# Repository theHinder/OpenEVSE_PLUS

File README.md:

# OpenEVSE_PLUS
README.md for OpenEVSE Hardware
Files SCH and BRD in Eagle format
License CC BY-SA 3.0
OpenEVSE Hardware

Current Version OpenEVSE_PLUS_v5.5.

OpenEVSE_PLUS_V5.5 - Moved GFCI Test pin to enable move of DC Relay outputs to PWM capable pins supporting full power closing reduced power holding in OpenEVSE 7.1.2+ firmware. Added GPIO pin pulled HIGH to auto detect board version in software to automatically set new/old pin values without requiring different firmware. Replaced 0.1" generic non-polarized connectors with JST PH for Serial (WiFi) and i2c (Display). Combined power and data connections for WiFi to reduce eliminate a screw terminal connector and simplify wiring harness. Replaced DC/DC converter with a TC1044S invert chip to generate -12v from +12v. 

OpenEVSE_PLUS_v5 - Optimized for reduced build time and high volume manufacturing of changing stations, removed most screw terminals and replaced with common connectors. Change from 2 single chanel opto-isolators for AC detection to 1 dual channel. Added ground connections to screw holes.

OpenEVSE_PLUS_v4 - Has 2 AC Detect chips like v1 + v2 plus the AC relay driver of v3. Added rectifier diodes to AC detect to improve detection in some conditions. Changed GFCI to individual pinout 4 pins.

OpenEVSE_PLUS_v3 - Removed 1 AC Detect chip and added AC relay driver. Added Current measurement circuit

OpenEVSE_PLUS_v2.5 - Added Current measurement circuit.

OpenEVSE_PLUS_v2 - modified GFCI pinout

OpenEVSE_PLUS_v1 - Inital version - Combined OpenEVSE v7 board and Advanced power supply into single board

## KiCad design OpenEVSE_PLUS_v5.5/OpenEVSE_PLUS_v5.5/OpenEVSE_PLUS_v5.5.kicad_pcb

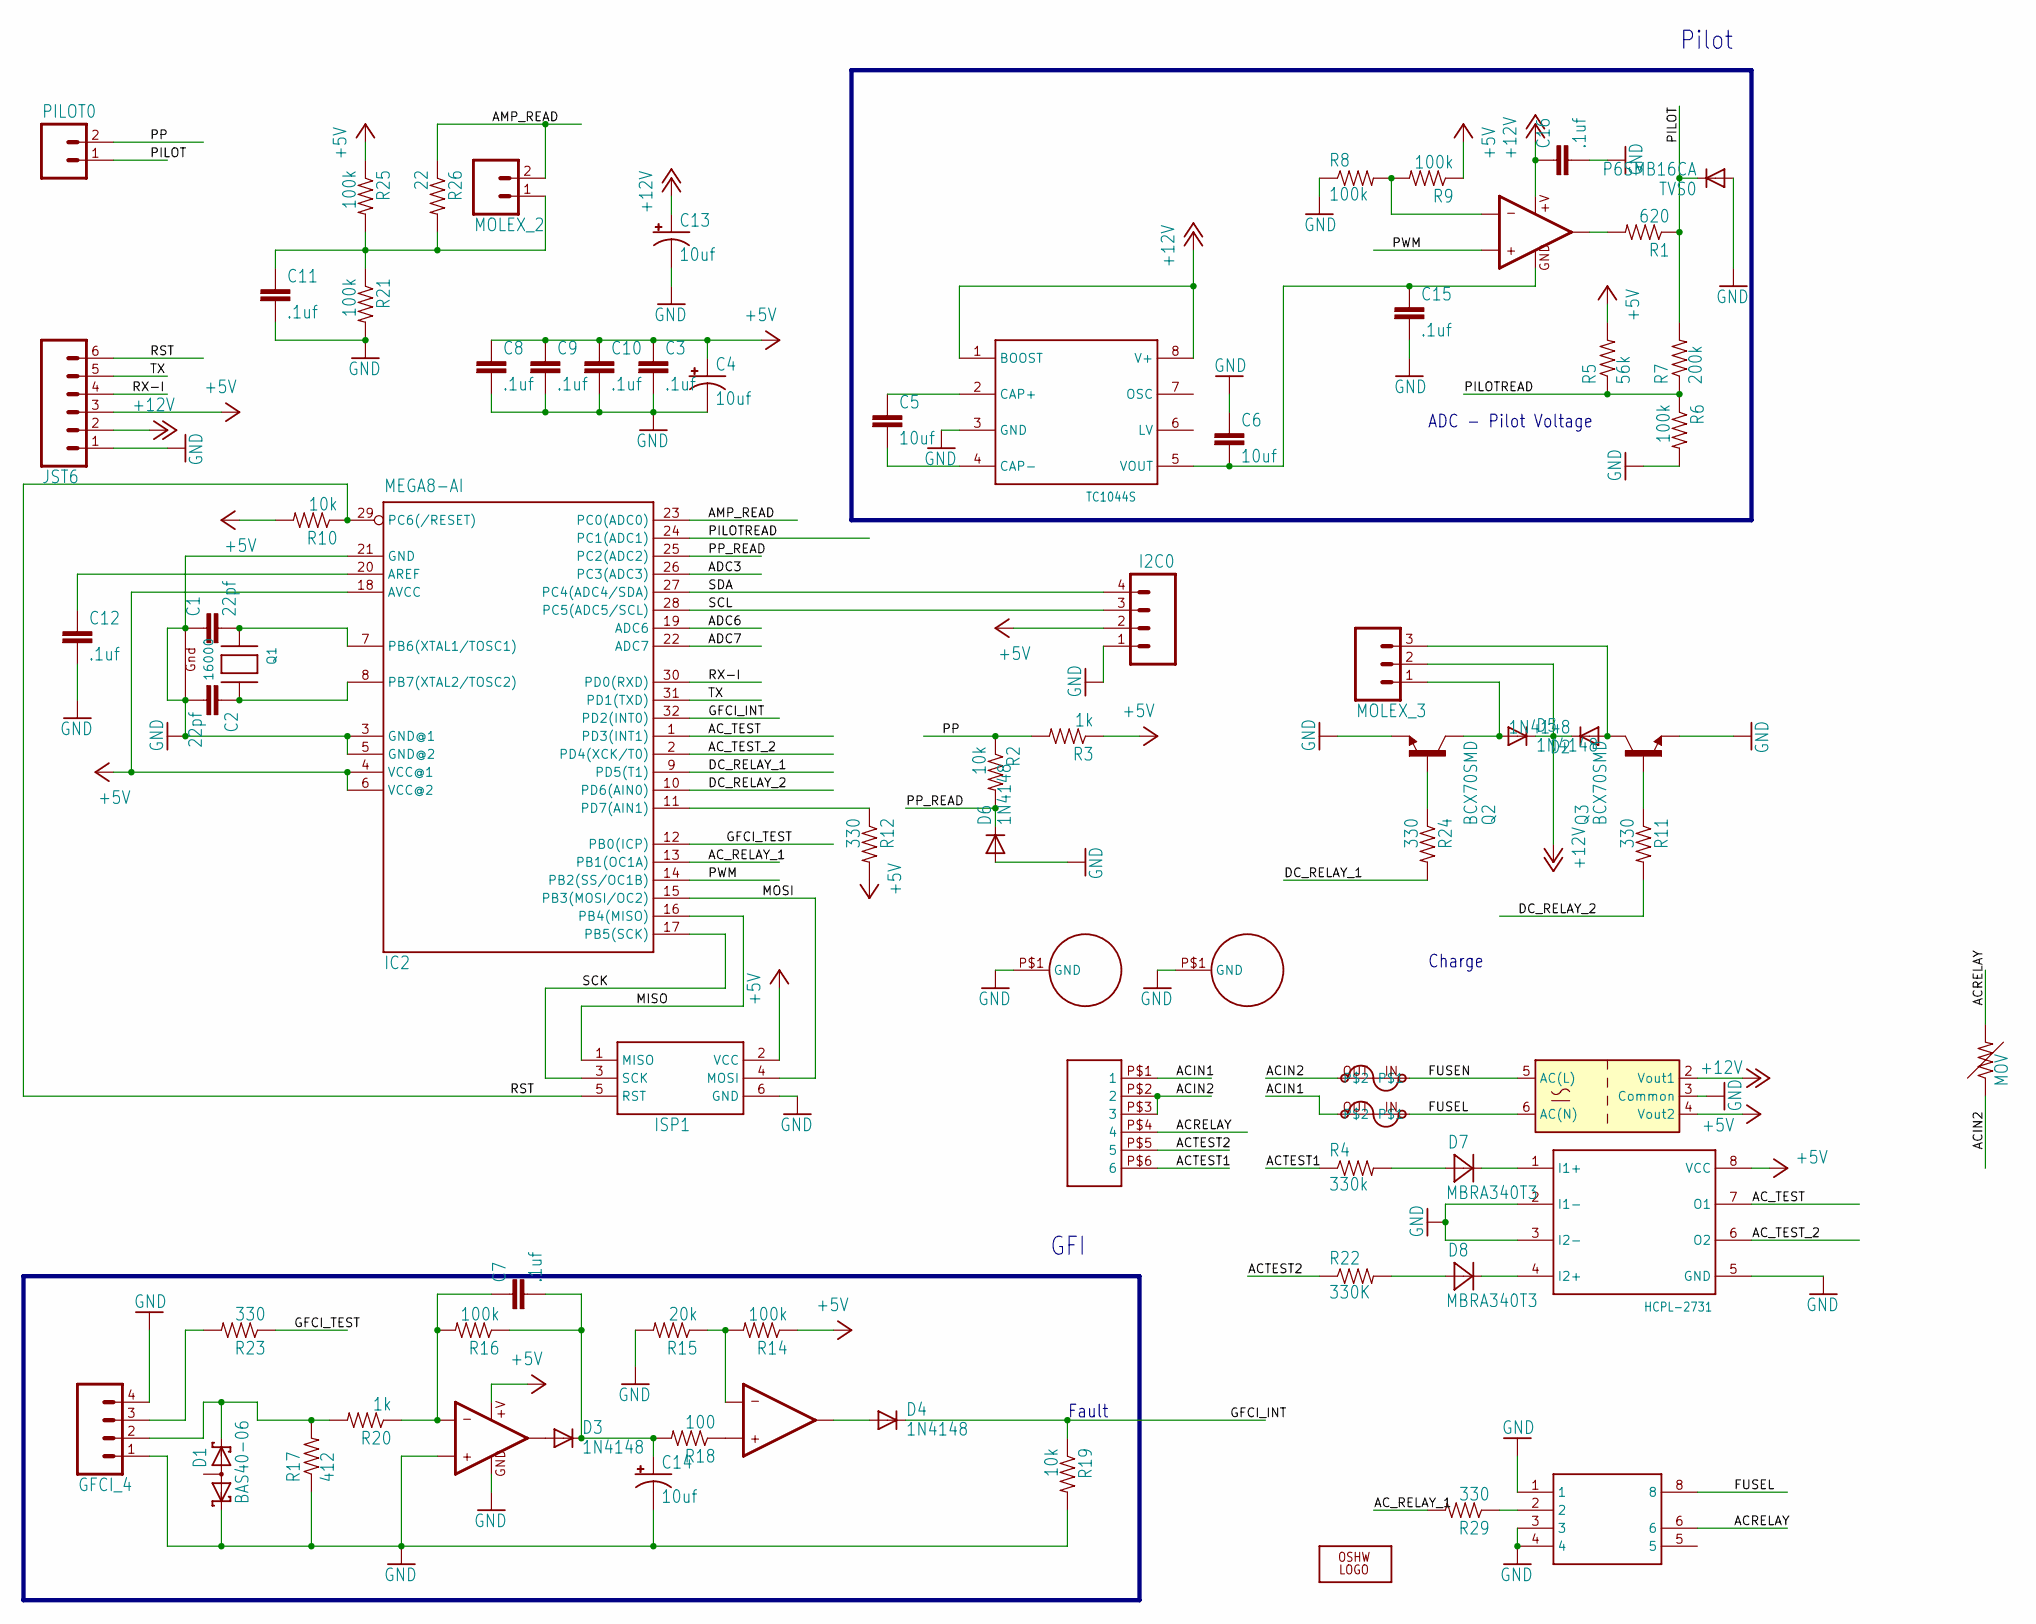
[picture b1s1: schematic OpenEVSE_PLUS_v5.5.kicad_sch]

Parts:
AC0: JST-VH-6
AMP_CT0: MOLEX_2
C1, C2: 22pf; 0805
C3, C7, C8, C9, C10, C11, C12, C15, C16: .1uf; 0805
C4, C13, C14: 10uf; EIA3216
C5, C6: 10uf; 1206-CAP
COMM0: JST6
D1: BAS40-06; SOT23
D2, D3, D4, D5, D6: 1N4148; SOD123
D7, D8: MBRA340T3; SMA
DC_RELAY0: MOLEX_3
F1, F2: BEL1AFUSE; BELFUSE1A
GFCI_CT0: GFCI_4
I2C0: M04JST-PTH-VERT; JST-4-PTH-VERT
IC1: HCPL-2731; DIP08
IC2: MEGA8-AI; TQFP32-08
IC3, IC4: LMV358; SO08
IC5: AQH1213; DIP7
IC6: TC1044S; SO-8
ISP1: AVRISP-6; AVRISP
LOGO1: OSHW_LOGO_8MILX0150-NT; OSHW_8X150_NOTEXT
PILOT0: M025MM; SCREWTERMINAL-5MM-2
PS1: MPM-04E-1205; Converter_ACDC_TRACO_TMLM-04_THT
Q1: 16000; NX3225
Q2, Q3: BCX70SMD; SOT23
R1: 620; 0805
R2, R10, R19: 10k; 0805
R3, R20: 1k; 0805
R4: 330k; AXIAL-0.4
R5: 56k; 0805
R6, R8, R9, R14, R16, R21, R25: 100k; 0805
R7: 200k; 0805
R11, R12, R23, R24, R29: 330; 0805
R15: 20k; 0805
R17: 412; 0805
R18: 100; 0805
R22: 330K; AXIAL-0.4
R26: 22; 0805
TVS0: P6SMB16CA; SMB
U$1: MOV
U$3, U$4: HOLE

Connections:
+5V: C3.1, C4.A (+), C8.1, C9.1, C10.1, COMM0.3, I2C0.2, IC1.8 (VCC), IC2.4 (VCC@1), IC2.6 (VCC@2), IC2.18 (AVCC), IC3.8 (+V), ISP1.2 (VCC), PS1.4 (Vout2), R3.1, R5.2, R9.1, R10.2, R12.2, R14.1, R25.1
+12V: C13.A (+), C16.1, COMM0.2, D2.C, D5.C, DC_RELAY0.2, IC4.8 (+V), IC6.1 (BOOST), IC6.8 (V+), PS1.2 (Vout1)
-12V: C6.2, C15.1, IC4.4 (GND), IC6.5 (VOUT)
ACIN1: AC0.P$1 (1), F2.OUT
ACIN2: AC0.P$2 (2), AC0.P$3 (3), F1.OUT, U$1.P$1 (1)
ACRELAY: AC0.P$4 (4), IC5.6, U$1.P$2 (2)
ACTEST1: AC0.P$6 (6), R4.P$1 (1)
ACTEST2: AC0.P$5 (5), R22.P$1 (1)
AC_RELAY_1: IC2.13 (PB1(OC1A)), R29.2
AC_TEST: IC1.7 (O1), IC2.1 (PD3(INT1))
AC_TEST_2: IC1.6 (O2), IC2.2 (PD4(XCK/T0))
ADC3: IC2.26 (PC3(ADC3))
ADC6: IC2.19 (ADC6)
ADC7: IC2.22 (ADC7)
AMP_READ: AMP_CT0.2, IC2.23 (PC0(ADC0)), R26.1
DC_RELAY_1: IC2.9 (PD5(T1)), R24.2
DC_RELAY_2: IC2.10 (PD6(AIN0)), R11.2
GFCI_INT: D4.C, IC2.32 (PD2(INT0)), R19.1
GFCI_TEST: IC2.12 (PB0(ICP)), R23.1
GND: C1.1, C2.2, C3.2, C4.C (-), C6.1, C8.2, C9.2, C10.2, C11.2, C12.2, C13.C (-), C14.C (-), C15.2, C16.2, COMM0.1, D1.1 (K1), D6.A, GFCI_CT0.1, GFCI_CT0.4, I2C0.1, IC1.2 (I1-), IC1.3 (I2-), IC1.5 (GND), IC2.3 (GND@1), IC2.5 (GND@2), IC2.21 (GND), IC3.3 (+IN1), IC3.4 (GND), IC5.1, IC5.3, IC5.4, IC6.3 (GND), ISP1.6 (GND), PS1.3 (Common), Q1.1 (G1), Q1.3 (G2), Q2.2 (E), Q3.2 (E), R6.2, R8.1, R15.2, R17.1, R19.2, R21.2, TVS0.A, U$3.P$1, U$4.P$1
MISO: IC2.16 (PB4(MISO)), ISP1.1 (MISO)
MOSI: IC2.15 (PB3(MOSI/OC2)), ISP1.4 (MOSI)
unnamed: D2.A, DC_RELAY0.3, Q3.3 (C)
unnamed: Q3.1 (B), R11.1
unnamed: C1.2, IC2.7 (PB6(XTAL1/TOSC1)), Q1.2 (X1)
unnamed: C2.1, IC2.8 (PB7(XTAL2/TOSC2)), Q1.4 (X2)
unnamed: D5.A, DC_RELAY0.1, Q2.3 (C)
unnamed: AMP_CT0.1, C11.1, R21.1, R25.2, R26.2
unnamed: C7.1, IC3.2 (-IN1), R16.2, R20.1
unnamed: D7.A, R4.P$2 (2)
unnamed: IC4.2 (-IN1), R8.2, R9.2
unnamed: IC4.1 (OUT1), R1.2
unnamed: D7.C, IC1.1 (I1+)
unnamed: D8.C, IC1.4 (I2+)
unnamed: D8.A, R22.P$2 (2)
unnamed: IC5.2, R29.1
unnamed: C5.1, IC6.2 (CAP+)
unnamed: D1.2 (K2), GFCI_CT0.2, R17.2, R20.2
unnamed: D3.A, IC3.1 (OUT1)
unnamed: GFCI_CT0.3, R23.2
unnamed: C7.2, C14.A (+), D3.C, R16.1, R18.2
unnamed: IC3.6 (-IN2), R14.2, R15.1
unnamed: D4.A, IC3.7 (OUT2)
unnamed: IC3.5 (+IN2), R18.1
unnamed: C5.2, IC6.4 (CAP-)
unnamed: IC2.11 (PD7(AIN1)), R12.1
unnamed: Q2.1 (B), R24.1
unnamed: C12.1, IC2.20 (AREF)
PILOT: PILOT0.1, R1.1, R7.2, TVS0.C
PILOTREAD: IC2.24 (PC1(ADC1)), R5.1, R6.1, R7.1
PP: PILOT0.2, R2.1, R3.2
PP_READ: D6.C, IC2.25 (PC2(ADC2)), R2.2
PWM: IC2.14 (PB2(SS/OC1B)), IC4.3 (+IN1)
RST: COMM0.6, IC2.29 (PC6(/RESET)), ISP1.5 (RST), R10.1
RX-I: COMM0.4, IC2.30 (PD0(RXD))
SCK: IC2.17 (PB5(SCK)), ISP1.3 (SCK)
SCL: I2C0.3, IC2.28 (PC5(ADC5/SCL))
SDA: I2C0.4, IC2.27 (PC4(ADC4/SDA))
TX: COMM0.5, IC2.31 (PD1(TXD))

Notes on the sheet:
ADC - Pilot Voltage
Pilot
Charge
Fault
GFI

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
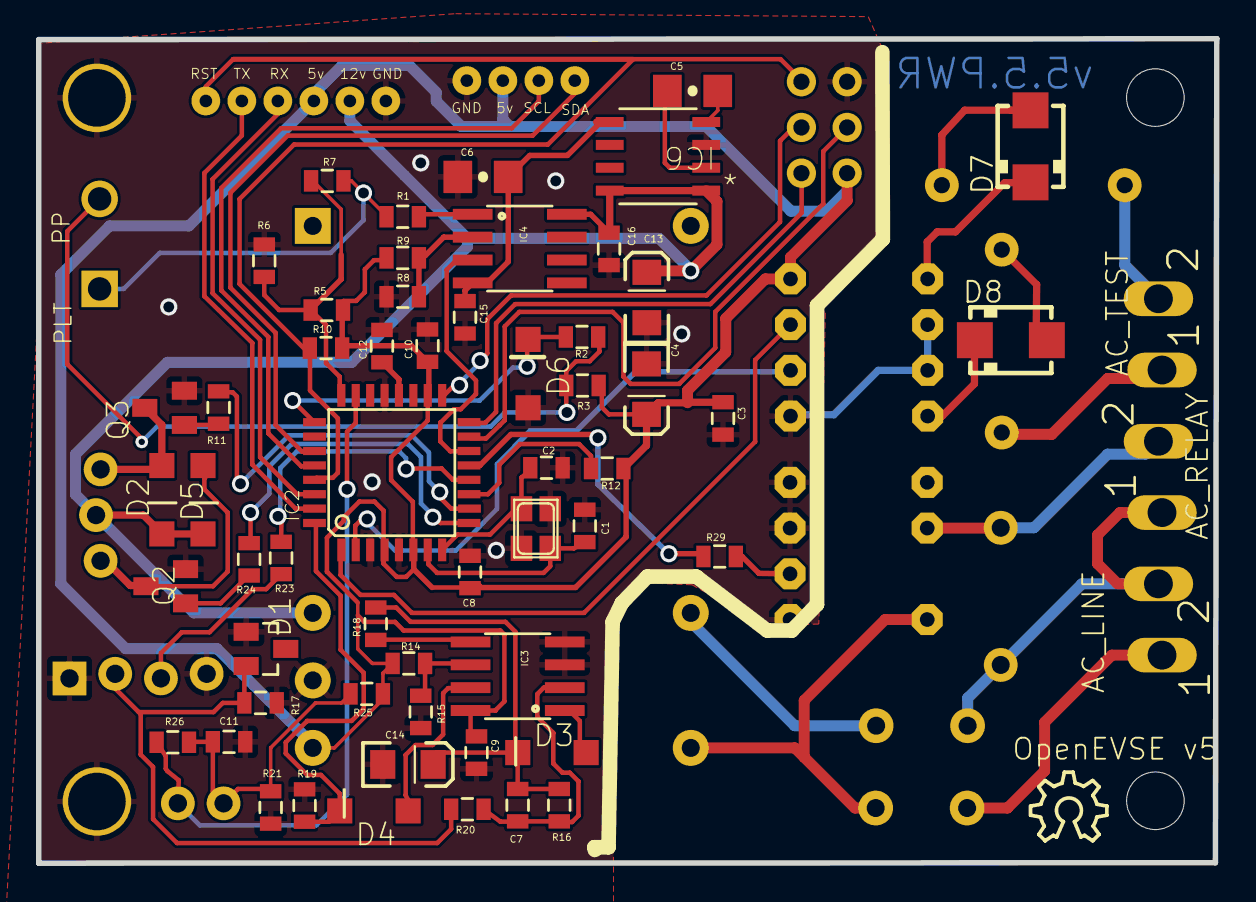
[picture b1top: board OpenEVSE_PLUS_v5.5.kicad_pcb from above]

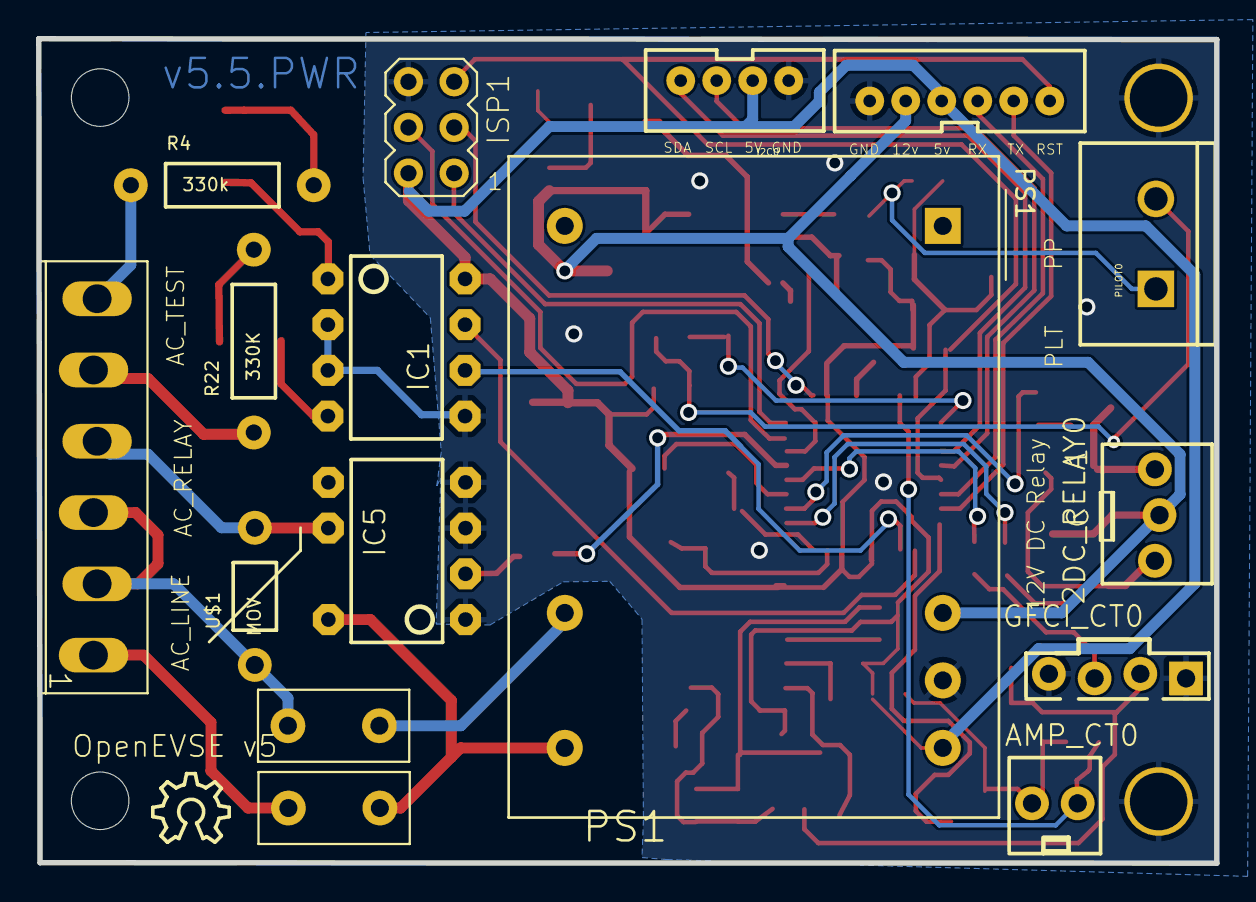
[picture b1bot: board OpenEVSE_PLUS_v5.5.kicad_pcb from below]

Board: 2 copper layers, 65.4 x 45.8 mm, 77 parts (17 on the bottom side), 58 nets.

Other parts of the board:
@HOLE0, @HOLE1: (no value)
LOGO2: OSHW_LOGO_8MILX0150-NT; OSHW_8X150_NOTEXT

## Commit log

2015-09-30 :octocat: Added .gitattributes & .gitignore files
2015-09-30 OpenEVSE_PLUS
    Move all source files from google code and web files
2015-09-30 Create README.md file
    Create file
2015-10-09 OpenEVSE Plus v1
2016-01-07 added details
2017-04-11 Updates to components
    Updated parts values so generic footprints report the correct part when exporting Eagle generated BOM.
    IC2 value 328P
    IC3 value LM358
    IC4 value LF353
    TVS value P6SMB16CA
    D1 value AZ23C5V6-7-F
2018-04-10 v5
    V5 files added
2018-04-11 v5 diagram
2018-04-23 Station Examples
    Drawing for "Standard" and "Advanced" Series. Additional drawing for 3 Phase.
2018-05-22 Add Datasheet
2018-05-22 Update Connection Diagram
    update to include part numbers for JST VH Housing and Pins and OpenEVSE GFCI and current coils
2018-10-23 Updated v5 info
2019-03-25 added pdf version of schematic
2019-03-25 changed pdf version of file name to not clash on non-case sensative operating systems
2021-01-18 Updated connection drawing
2021-04-01 Added v5.5
    Added change log for v 5.5.
2021-04-14 Upload files for OpenEVSE PLUS v 5.5
    Upload source files for OpenEVSE PLUS v 5.5
2021-06-02 Update README.md
    add TC1044S into v5.5
2021-06-02 Update README.md
    fixed typos
2021-06-02 Add files via upload
    Drawings for Advanced station and v5.5 connections
2021-06-05 Add files via upload
    JPEG
2023-06-02 Advanced_2023
    Update drawing
2024-04-03 Convert to kicad
2024-04-14 WIP new power module TMLM 04225
